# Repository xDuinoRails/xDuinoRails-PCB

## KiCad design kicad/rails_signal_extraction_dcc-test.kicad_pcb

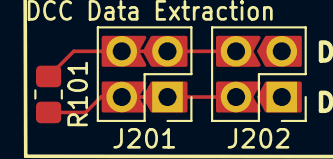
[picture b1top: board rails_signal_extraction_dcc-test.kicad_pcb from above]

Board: 2 copper layers, 3 parts (0 on the bottom side), 2 nets.

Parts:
J201, J202: Conn_02x02_Odd_Even; PinHeaderJP_2x02_P2.54mm_Vertical
R101: 22k; R_0805_2012Metric_Pad1.20x1.40mm_HandSolder

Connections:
/J_DCC1: J201.3, J201.4, J202.4, R101.1
/J_DCC_MM_SIGNAL: J201.1, J201.2, J202.2, R101.2

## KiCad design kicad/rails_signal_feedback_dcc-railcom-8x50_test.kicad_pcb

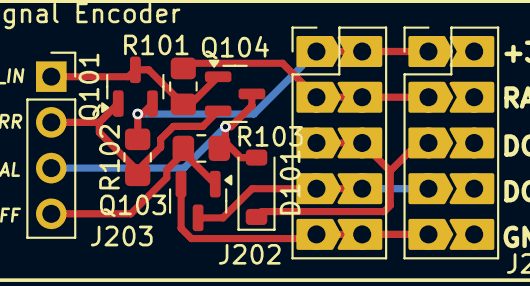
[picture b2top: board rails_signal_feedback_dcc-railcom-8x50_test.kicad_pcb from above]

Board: 2 copper layers, 10 parts (0 on the bottom side), 9 nets.

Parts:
D101: 1N5819W; D_SOD-123
J201, J202: Conn_02x05_Odd_Even; PinHeaderJP_2x05_P2.54mm_Vertical
J203: Conn_01x04; PinSocket_1x04_P2.54mm_Vertical
Q101, Q104: S8550; 8x50_SOT-23
Q103: S8050; 8x50_SOT-23
R101, R103: 10k; R_0805_2012Metric_Pad1.20x1.40mm_HandSolder
R102: 20R; R_0805_2012Metric_Pad1.20x1.40mm_HandSolder

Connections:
0: J201.9, J202.9, J202.10, Q103.1 (E)
/+J_3v3: J201.1, J202.1, J202.2, Q101.1 (E), R102.2
/J_DCC0: D101.1 (K), J201.5, J202.5, J202.6
/J_DCC1: J201.7, J202.7, J202.8, Q103.3 (C)
/J_RAILCOM_DATA: J201.3, J202.3, J202.4, R101.2
/_TST_RC_CURR: J203.2, Q101.2 (B), Q104.1 (E), R102.1
/_TST_RC_DATA_IN: J203.1, Q101.3 (C), Q104.2 (B), R101.1
/_TST_RC_ON_OFF: J203.4, Q103.2 (B), R103.2
/_TST_RC_SIGNAL: D101.2 (A), J203.3, Q104.3 (C), R103.1

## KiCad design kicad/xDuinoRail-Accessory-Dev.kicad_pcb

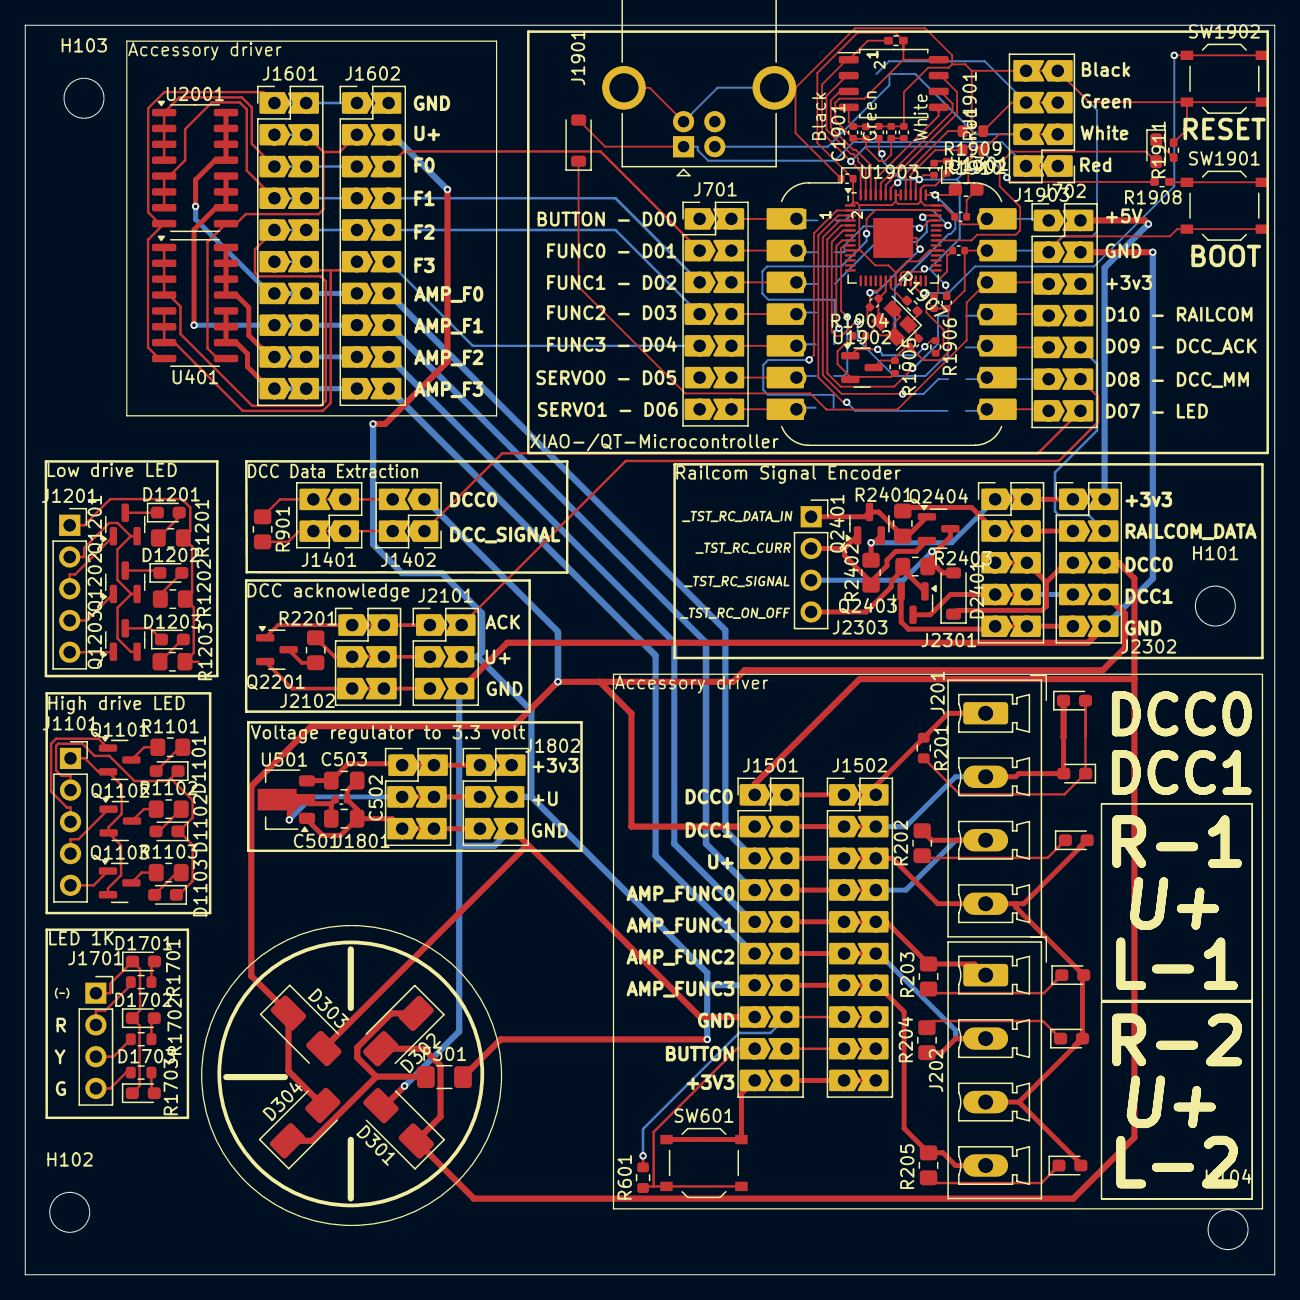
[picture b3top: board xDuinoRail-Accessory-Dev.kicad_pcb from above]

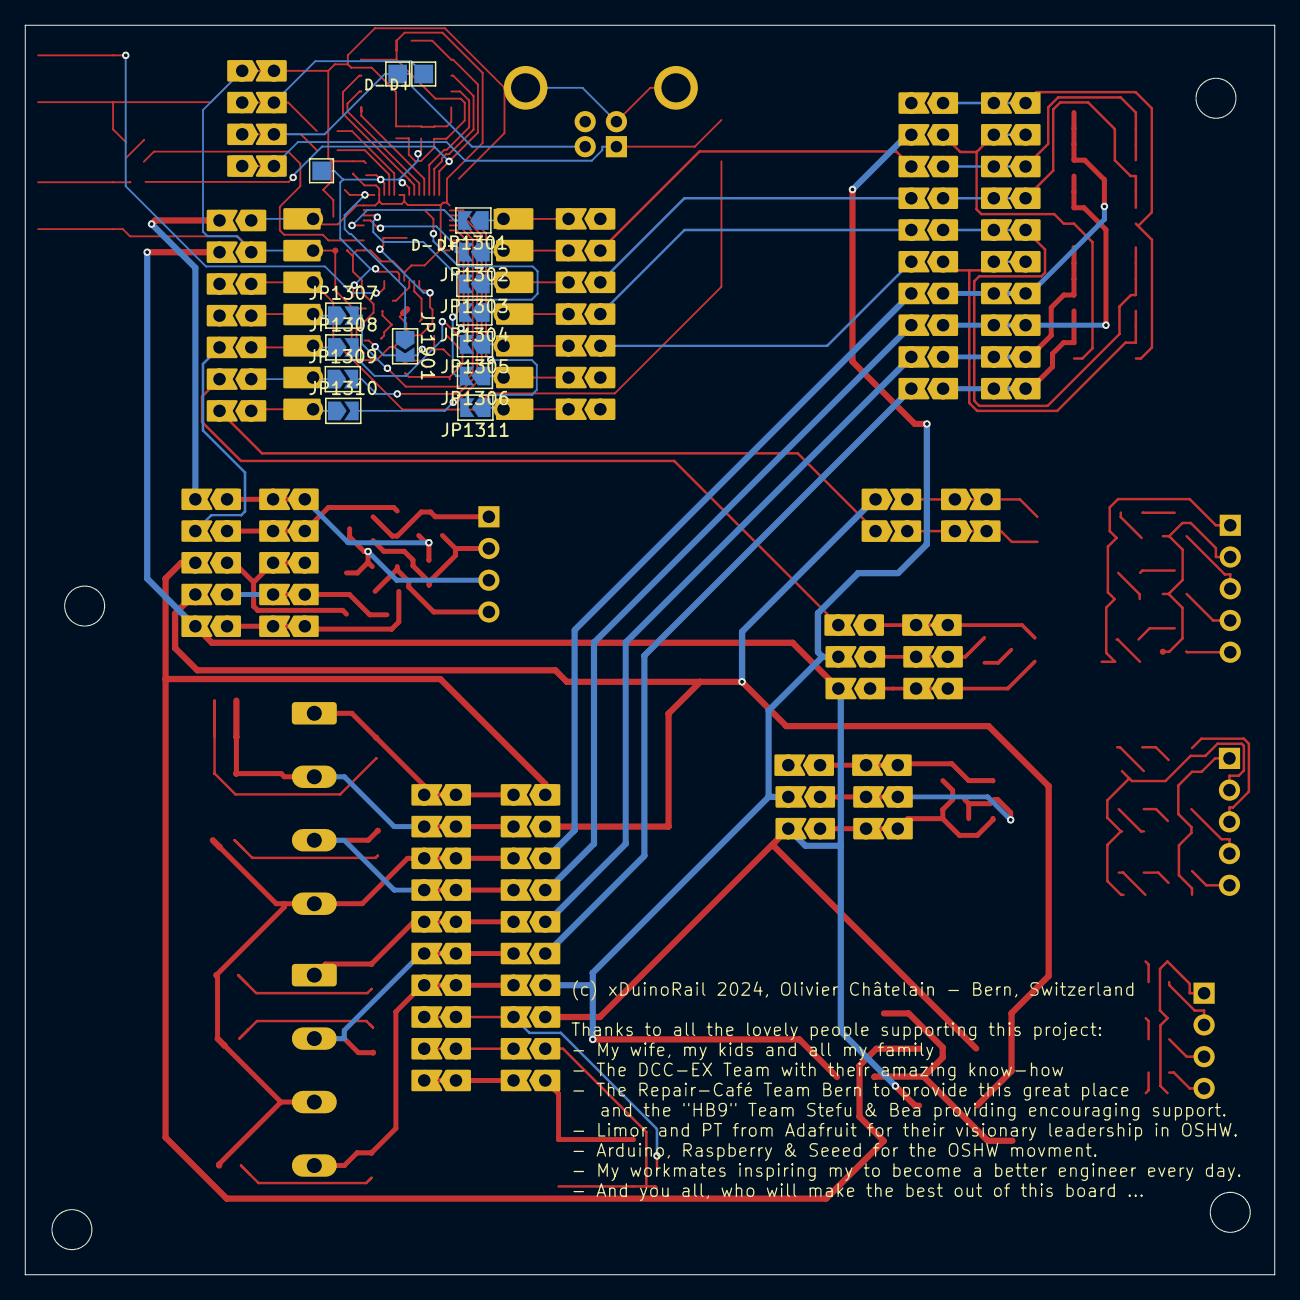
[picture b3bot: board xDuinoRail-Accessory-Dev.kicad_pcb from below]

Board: 2 copper layers, 100.0 x 100.0 mm, 132 parts (15 on the bottom side), 133 nets.

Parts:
C501, C503: 47uF; C_0805_2012Metric_Pad1.18x1.45mm_HandSolder
C502, C1907, C1909: 1u; C_0402_1005Metric
C1901, C1905, C1906, C1908, C1910, C1911, C1912, C1913, C1914, C1915: 100n; C_0402_1005Metric
C1902: 10n C0G; C_0603_1608Metric_Pad1.08x0.95mm_HandSolder
C1903, C1904: 18p; C_0402_1005Metric
D201, D1102, D1702: LED_YELLOW; LED_0603_1608Metric_Pad1.05x0.95mm_HandSolder
D202: LED_WHITE; LED_0603_1608Metric_Pad1.05x0.95mm_HandSolder
D203, D205, D1101, D1201, D1202, D1203, D1701, D1902: LED_RED; LED_0603_1608Metric_Pad1.05x0.95mm_HandSolder
D204, D206, D1103, D1703: LED_GREEN; LED_0603_1608Metric_Pad1.05x0.95mm_HandSolder
D301, D302, D303, D304: SS14; D_SMA
D1901: B5819W; D_SOD-123
D2401: 1N5819W; D_SOD-123
F301: SRF1206P150; Fuse_1206_3216Metric_Pad1.42x1.75mm_HandSolder
H101, H102, H103, H104: MountingHole; MountingHole_3.2mm_M3
J201, J202: Conn_01x04; PhoenixContact_MCV_1,5_4-G-5.08_1x04_P5.08mm_Vertical
J701, J702: Conn_02x07_Odd_Even; PinHeaderJP_2x07_P2.54mm_Vertical
J1101, J1201: Conn_01x05; PinSocket_1x05_P2.54mm_Vertical
J1401, J1402: Conn_02x02_Odd_Even; PinHeaderJP_2x02_P2.54mm_Vertical
J1501, J1502, J1601, J1602: Conn_02x10_Odd_Even; PinHeaderJP_2x10_P2.54mm_Vertical
J1701, J2303: Conn_01x04; PinSocket_1x04_P2.54mm_Vertical
J1801, J1802, J2101, J2102: Conn_02x03_Odd_Even; PinHeaderJP_2x03_P2.54mm_Vertical
J1901: USB_B; USB_B_OST_USB-B1HSxx_Horizontal
J1903: Conn_02x04_Odd_Even; PinHeaderJP_2x04_P2.54mm_Vertical
J2301, J2302: Conn_02x05_Odd_Even; PinHeaderJP_2x05_P2.54mm_Vertical
JP1301, JP1302, JP1303, JP1304, JP1305, JP1306, JP1307, JP1308, JP1309, JP1310, JP1311: SolderJumper_2_Open; SolderJumper-2_P1.3mm_Open_TrianglePad1.0x1.5mm
JP1901: VREF; SolderJumper-2_P1.3mm_Open_TrianglePad1.0x1.5mm
Q1101, Q1102, Q1103, Q2401, Q2404: S8550; 8x50_SOT-23
Q1201, Q1202, Q1203, Q2201, Q2403: S8050; 8x50_SOT-23
R201, R601: 10k; R_0603_1608Metric
R202, R203, R204, R205, R1101, R1102, R1103, R1201, R1202, R1203: 1k; R_0805_2012Metric_Pad1.20x1.40mm_HandSolder
R901: 22k; R_0805_2012Metric_Pad1.20x1.40mm_HandSolder
R1701, R1702, R1703: 1k; R_0603_1608Metric
R1901: DNP; R_0402_1005Metric_Pad0.72x0.64mm_HandSolder
R1904: 680R; R_0402_1005Metric
R1905: 3k3; R_0402_1005Metric
R1906: 150R; R_0402_1005Metric
R1907, R1908, R1911: 1k; R_0402_1005Metric_Pad0.72x0.64mm_HandSolder
R1909, R1910: 27R; R_0603_1608Metric
R2201: 150R; R_0805_2012Metric_Pad1.20x1.40mm_HandSolder
R2401, R2403: 10k; R_0805_2012Metric_Pad1.20x1.40mm_HandSolder
R2402: 20R; R_0805_2012Metric_Pad1.20x1.40mm_HandSolder
SW601: TS-1187A-B-A-B; SW_Push_1P1T_XKB_TS-1187A
SW1901: BOOTSEL; SW_Push_1P1T_XKB_TS-1187A
SW1902: RESET; SW_Push_1P1T_XKB_TS-1187A
TP1901: VREG; TestPoint_Pad_1.5x1.5mm
TP1902: D+; TestPoint_Pad_1.5x1.5mm
TP1903: D-; TestPoint_Pad_1.5x1.5mm
U401, U2001: ULN2003A; SOIC-16_3.9x9.9mm_P1.27mm
U501: HT75xx-1-SOT89; SOT-89-3
U1301: MOUDLE-SEEEDUINO-XIAO-ESP32C3; XIAO_THT_SMD
U1901: W25Q128JVSIQ; SOIC-8_5.23x5.23mm_P1.27mm
U1902: TL431DBZ; SOT-23
U1903: RP2040; QFN-56-1EP_7x7mm_P0.4mm_EP3.2x3.2mm
Y1901: ECS-120-12-36-AGN-TR3; Crystal_SMD_2520-4Pin_2.5x2.0mm

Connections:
0: J2101.5, J2102.5, J2102.6, J2301.9, J2301.10, J2302.9, Q2201.1 (E), Q2403.1 (E)
+1V1: C1905.1, C1906.1, C1907.1, TP1901.1, U1903.23 (DVDD), U1903.45 (VREG_VOUT), U1903.50 (DVDD)
+3V3: J702.2, J1101.1, J1201.1, J2302.2, Q1101.1 (E), Q1102.1 (E), Q1103.1 (E), R1201.1, R1202.1, R1203.1
+5V: D1901.1 (K), J702.5, U1301.12 (3V3)
+U: F301.2, J1501.13, J1602.4, J1802.4, J2101.4
/AMP_FUNC0: J1501.5, J1602.14
/AMP_FUNC1: J1501.7, J1602.16
/AMP_FUNC2: J1501.9, J1602.18
/AMP_FUNC3: J1501.11, J1602.20
/DCC0: D301.1 (K), D302.2 (A), J1501.1, J2302.6
/DCC1: D303.1 (K), D304.2 (A), J1402.3, J1501.3, J2302.8
/DCC_ACK: J702.12, J2101.2
/DCC_MM_SIGNAL: J702.14, J1402.1
/FUNC0: J701.3, J1602.6
/FUNC1: J701.5, J1602.8
/FUNC2: J701.7, J1602.10
/FUNC3: J701.9, J1602.12
/RAILCOM_DATA: J702.10, J2302.4
/acc-conn-screw-01x08-test/+3V3: J1501.19, SW601.1
/acc-conn-screw-01x08-test/BUTTON: J1501.17, R601.1, SW601.2
/acc-conn-screw-01x08-test/J_+3V3: J1501.20, J1502.19, J1502.20
/acc-conn-screw-01x08-test/J_AMP_FUNC0: J201.3, J1501.8, J1502.7, J1502.8, R202.1
/acc-conn-screw-01x08-test/J_AMP_FUNC1: J202.1, J1501.10, J1502.9, J1502.10, R203.1
/acc-conn-screw-01x08-test/J_AMP_FUNC2: J202.2, J1501.12, J1502.11, J1502.12, R204.1
/acc-conn-screw-01x08-test/J_AMP_FUNC3: J202.4, J1501.14, J1502.13, J1502.14, R205.1
/acc-conn-screw-01x08-test/J_BUTTON: J1501.18, J1502.17, J1502.18
/acc-conn-screw-01x08-test/J_DCC0: J201.1, J1501.2, J1502.1, J1502.2, R201.1
/acc-conn-screw-01x08-test/J_DCC1: D201.2 (A), D202.1 (K), J201.2, J1501.4, J1502.3, J1502.4
/acc-conn-screw-01x08-test/J_GND: J1501.16, J1502.15, J1502.16, R601.2
/acc-conn-screw-01x08-test/J_U+: D203.2 (A), D204.2 (A), D205.2 (A), D206.2 (A), J201.4, J202.3, J1501.6, J1502.5, J1502.6
/acc-mcu-xiao-test/J_+3v3: C1901.1, C1908.1, C1909.1, C1910.1, C1911.1, C1912.1, C1913.1, C1914.1, C1915.1, J702.1, R1901.1, R1906.2, U1301.14 (5V), U1901.8 (VCC), U1903.1 (IOVDD), U1903.10 (IOVDD), U1903.22 (IOVDD), U1903.33 (IOVDD), U1903.42 (IOVDD), U1903.44 (VREG_IN), U1903.48 (USB_VDD), U1903.49 (IOVDD)
/acc-mcu-xiao-test/J_BUTTON: J701.2, JP1301.1 (A), U1301.1 (A0)
/acc-mcu-xiao-test/J_DCC_ACK: J702.11, JP1309.1 (A), U1301.9 (A8_SCK)
/acc-mcu-xiao-test/J_DCC_MM: J702.13, JP1310.1 (A), U1301.8 (A7_RX)
/acc-mcu-xiao-test/J_FUNC0: J701.4, JP1302.1 (A), U1301.2 (A1)
/acc-mcu-xiao-test/J_FUNC1: J701.6, JP1303.1 (A), U1301.3 (A2)
/acc-mcu-xiao-test/J_FUNC2: J701.8, JP1304.1 (A), U1301.4 (A3)
/acc-mcu-xiao-test/J_FUNC3: J701.10, JP1305.1 (A), U1301.5 (A4_SDA)
/acc-mcu-xiao-test/J_GND: C1901.2, C1902.2, C1903.2, C1904.2, C1905.2, C1906.2, C1907.2, C1908.2, C1909.2, C1910.2, C1911.2, C1912.2, C1913.2, C1914.2, C1915.2, J702.3, J1901.4 (GND), J1901.5 (Shield), J1903.7, J1903.8, R1905.1, R1911.2, SW1901.2, SW1902.2, U1301.13 (GND), U1901.4 (GND), U1902.3 (A), U1903.19 (TESTEN), U1903.57 (GND), Y1901.2, Y1901.4
/acc-mcu-xiao-test/J_LED: J702.7, JP1307.1 (A), U1301.11 (A10_MOSI)
/acc-mcu-xiao-test/J_RAILCOM: J702.9, JP1308.1 (A), U1301.10 (A9_MISO)
/acc-mcu-xiao-test/J_SERVO0: J701.12, JP1306.1 (A), U1301.6 (A5_SCL)
/acc-mcu-xiao-test/J_SERVO1: J701.14, JP1311.1 (A), U1301.7 (A6_TX)
/acc-mcu-xiao-test/acc-mcu-xiao/GPIO0: JP1311.2 (B), U1903.2 (GPIO0)
/acc-mcu-xiao-test/acc-mcu-xiao/GPIO1: JP1310.2 (B), U1903.3 (GPIO1)
/acc-mcu-xiao-test/acc-mcu-xiao/GPIO2: JP1309.2 (B), U1903.4 (GPIO2)
/acc-mcu-xiao-test/acc-mcu-xiao/GPIO3: JP1307.2 (B), U1903.5 (GPIO3)
/acc-mcu-xiao-test/acc-mcu-xiao/GPIO4: JP1308.2 (B), U1903.6 (GPIO4)
/acc-mcu-xiao-test/acc-mcu-xiao/GPIO6: JP1305.2 (B), U1903.8 (GPIO6)
/acc-mcu-xiao-test/acc-mcu-xiao/GPIO7: JP1306.2 (B), U1903.9 (GPIO7)
/acc-mcu-xiao-test/acc-mcu-xiao/GPIO23: D1902.2 (A), U1903.35 (GPIO23)
/acc-mcu-xiao-test/acc-mcu-xiao/GPIO26: JP1301.2 (B), U1903.38 (GPIO26_ADC0)
/acc-mcu-xiao-test/acc-mcu-xiao/GPIO27: JP1302.2 (B), U1903.39 (GPIO27_ADC1)
/acc-mcu-xiao-test/acc-mcu-xiao/GPIO28: JP1303.2 (B), U1903.40 (GPIO28_ADC2)
/acc-mcu-xiao-test/acc-mcu-xiao/GPIO29: JP1304.2 (B), U1903.41 (GPIO29_ADC3)
/acc-mcu-xiao-test/acc-mcu-xiao/mcu_rp2040-onboard/2v5_VREF: R1904.1, R1905.2, U1902.2 (REF)
/acc-mcu-xiao-test/acc-mcu-xiao/mcu_rp2040-onboard/3V0_VREF: JP1901.2 (B), R1904.2, R1906.1, U1902.1 (K)
/acc-mcu-xiao-test/acc-mcu-xiao/mcu_rp2040-onboard/ADC_VREF: C1902.1, JP1901.1 (A), U1903.43 (ADC_AVDD)
/acc-mcu-xiao-test/acc-mcu-xiao/mcu_rp2040-onboard/D+: J1903.5, J1903.6, R1909.1, TP1902.1
/acc-mcu-xiao-test/acc-mcu-xiao/mcu_rp2040-onboard/D-: J1901.2 (D-), J1903.3, J1903.4, R1910.1, TP1903.1
/acc-mcu-xiao-test/acc-mcu-xiao/mcu_rp2040-onboard/DN: R1910.2, U1903.46 (USB_DM)
/acc-mcu-xiao-test/acc-mcu-xiao/mcu_rp2040-onboard/DP: R1909.2, U1903.47 (USB_DP)
/acc-mcu-xiao-test/acc-mcu-xiao/mcu_rp2040-onboard/QSPI_SCLK: U1901.6 (CLK), U1903.52 (QSPI_SCLK)
/acc-mcu-xiao-test/acc-mcu-xiao/mcu_rp2040-onboard/QSPI_SD0: U1901.5 (DI(IO0)), U1903.53 (QSPI_SD0)
/acc-mcu-xiao-test/acc-mcu-xiao/mcu_rp2040-onboard/QSPI_SD1: U1901.2 (DO(IO1)), U1903.55 (QSPI_SD1)
/acc-mcu-xiao-test/acc-mcu-xiao/mcu_rp2040-onboard/QSPI_SD2: U1901.3 (IO2), U1903.54 (QSPI_SD2)
/acc-mcu-xiao-test/acc-mcu-xiao/mcu_rp2040-onboard/QSPI_SD3: U1901.7 (IO3), U1903.51 (QSPI_SD3)
/acc-mcu-xiao-test/acc-mcu-xiao/mcu_rp2040-onboard/QSPI_SS: R1901.2, R1908.1, U1901.1 (~CS), U1903.56 (QSPI_SS)
/acc-mcu-xiao-test/acc-mcu-xiao/mcu_rp2040-onboard/RESET_RUN: SW1902.1, U1903.26 (RUN)
/acc-mcu-xiao-test/acc-mcu-xiao/mcu_rp2040-onboard/XIN: C1903.1, U1903.20 (XIN), Y1901.3
/acc-mcu-xiao-test/acc-mcu-xiao/mcu_rp2040-onboard/XOUT: R1907.1, U1903.21 (XOUT)
/acc-switch-driver-dual-test/J_AMP_FUNC0: J1601.13, J1601.14, J1602.13, U2001.13 (O4), U2001.14 (O3), U2001.15 (O2), U2001.16 (O1)
/acc-switch-driver-dual-test/J_AMP_FUNC1: J1601.15, J1601.16, J1602.15, U2001.10 (O7), U2001.11 (O6), U2001.12 (O5)
/acc-switch-driver-dual-test/J_AMP_FUNC2: J1601.17, J1601.18, J1602.17, U401.13 (O4), U401.14 (O3), U401.15 (O2), U401.16 (O1)
/acc-switch-driver-dual-test/J_AMP_FUNC3: J1601.19, J1601.20, J1602.19, U401.10 (O7), U401.11 (O6), U401.12 (O5)
/acc-switch-driver-dual-test/J_FUNC0: J1601.5, J1601.6, J1602.5, U2001.1 (I1), U2001.2 (I2), U2001.3 (I3), U2001.4 (I4)
/acc-switch-driver-dual-test/J_FUNC1: J1601.7, J1601.8, J1602.7, U2001.5 (I5), U2001.6 (I6), U2001.7 (I7)
/acc-switch-driver-dual-test/J_FUNC2: J1601.9, J1601.10, J1602.9, U401.1 (I1), U401.2 (I2), U401.3 (I3), U401.4 (I4)
/acc-switch-driver-dual-test/J_FUNC3: J1601.11, J1601.12, J1602.11, U401.5 (I5), U401.6 (I6), U401.7 (I7)
/acc-switch-driver-dual-test/J_GND: J1601.1, J1601.2, J1602.1, U401.8 (GND), U2001.8 (GND)
/acc-switch-driver-dual-test/J_U+: J1601.3, J1601.4, J1602.3, U401.9 (COM), U2001.9 (COM)
/led-array/LED_HIGH1: J1101.3, Q1101.2 (B)
/led-array/LED_HIGH2: J1101.4, Q1102.2 (B)
/led-array/LED_HIGH3: J1101.5, Q1103.2 (B)
/led-array/LED_LOW1: J1201.3, Q1201.2 (B)
/led-array/LED_LOW2: J1201.4, Q1202.2 (B)
/led-array/LED_LOW3: J1201.5, Q1203.2 (B)
/leds-1k-ryg/GND: D1701.1 (K), D1702.1 (K), D1703.1 (K), J1701.1
/leds-1k-ryg/LED1: J1701.2, R1701.1
/leds-1k-ryg/LED2: J1701.3, R1702.1
/leds-1k-ryg/LED3: J1701.4, R1703.1
/rails_power_ac-dc-bridge-medium-x/+U_UNFUSED: D302.1 (K), D304.1 (K), F301.1
/rails_power_dc-dc-ldo-3v3_100mA-test/J_3v3: C503.1, J1801.1, J1801.2, J1802.1, U501.3 (VOUT)
/rails_power_dc-dc-ldo-3v3_100mA-test/J_GND: C501.2, C502.2, C503.2, J1801.5, J1801.6, J1802.5, U501.1 (GND)
/rails_power_dc-dc-ldo-3v3_100mA-test/J_U+: C501.1, C502.1, J1801.3, J1801.4, J1802.3, U501.2 (VIN)
/rails_signal_combined-test/rails_signal_acknowledge_dcc-test/J_DCC_ACK: J2101.1, J2102.1, J2102.2, Q2201.2 (B)
/rails_signal_combined-test/rails_signal_acknowledge_dcc-test/J_U+: J2101.3, J2102.3, J2102.4, R2201.2
/rails_signal_combined-test/rails_signal_acknowledge_dcc-test/rails-signal-ackn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: Q2201.3 (C), R2201.1
/rails_signal_combined-test/rails_signal_extraction_dcc-test/J_DCC1: J1401.3, J1401.4, J1402.4, R901.1
/rails_signal_combined-test/rails_signal_extraction_dcc-test/J_DCC_MM_SIGNAL: J1401.1, J1401.2, J1402.2, R901.2
/rails_signal_combined-test/rails_signal_feedback_dcc-railcom-8x50_test/+J_3v3: J2301.1, J2301.2, J2302.1, Q2401.1 (E), R2402.2
/rails_signal_combined-test/rails_signal_feedback_dcc-railcom-8x50_test/J_DCC0: D2401.1 (K), J2301.5, J2301.6, J2302.5
/rails_signal_combined-test/rails_signal_feedback_dcc-railcom-8x50_test/J_DCC1: J2301.7, J2301.8, J2302.7, Q2403.3 (C)
/rails_signal_combined-test/rails_signal_feedback_dcc-railcom-8x50_test/J_RAILC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: J2301.3, J2301.4, J2302.3, R2401.2
/rails_signal_combined-test/rails_signal_feedback_dcc-railcom-8x50_test/_TST_RC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: J2303.2, Q2401.2 (B), Q2404.1 (E), R2402.1
/rails_signal_combined-test/rails_signal_feedback_dcc-railcom-8x50_test/_TST_RC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: J2303.1, Q2401.3 (C), Q2404.2 (B), R2401.1
/rails_signal_combined-test/rails_signal_feedback_dcc-railcom-8x50_test/_TST_RC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: J2303.4, Q2403.2 (B), R2403.2
/rails_signal_combined-test/rails_signal_feedback_dcc-railcom-8x50_test/_TST_RC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: D2401.2 (A), J2303.3, Q2404.3 (C), R2403.1
GND: D301.2 (A), D303.2 (A), D1101.1 (K), D1102.1 (K), D1103.1 (K), J702.4, J1101.2, J1201.2, J1501.15, J1602.2, J1802.6, J2101.6, J2302.10, Q1201.1 (E), Q1202.1 (E), Q1203.1 (E)
unnamed: C1904.1, R1907.2, Y1901.1
unnamed: D201.1 (K), D202.2 (A), R201.2
unnamed: D203.1 (K), R202.2
unnamed: D204.1 (K), R203.2
unnamed: D205.1 (K), R204.2
unnamed: D206.1 (K), R205.2
unnamed: D1101.2 (A), R1101.2
unnamed: D1102.2 (A), R1102.2
unnamed: D1103.2 (A), R1103.2
unnamed: D1201.2 (A), R1201.2
unnamed: D1201.1 (K), Q1201.3 (C)
unnamed: D1202.2 (A), R1202.2
unnamed: D1202.1 (K), Q1202.3 (C)
unnamed: D1203.2 (A), R1203.2
unnamed: D1203.1 (K), Q1203.3 (C)
unnamed: D1701.2 (A), R1701.2
unnamed: D1702.2 (A), R1702.2
unnamed: D1703.2 (A), R1703.2
unnamed: D1902.1 (K), R1911.1
unnamed: Q1101.3 (C), R1101.1
unnamed: Q1102.3 (C), R1102.1
unnamed: Q1103.3 (C), R1103.1
unnamed: R1908.2, SW1901.1
VBUS: D1901.2 (A), J1901.1 (VBUS), J1903.1, J1903.2

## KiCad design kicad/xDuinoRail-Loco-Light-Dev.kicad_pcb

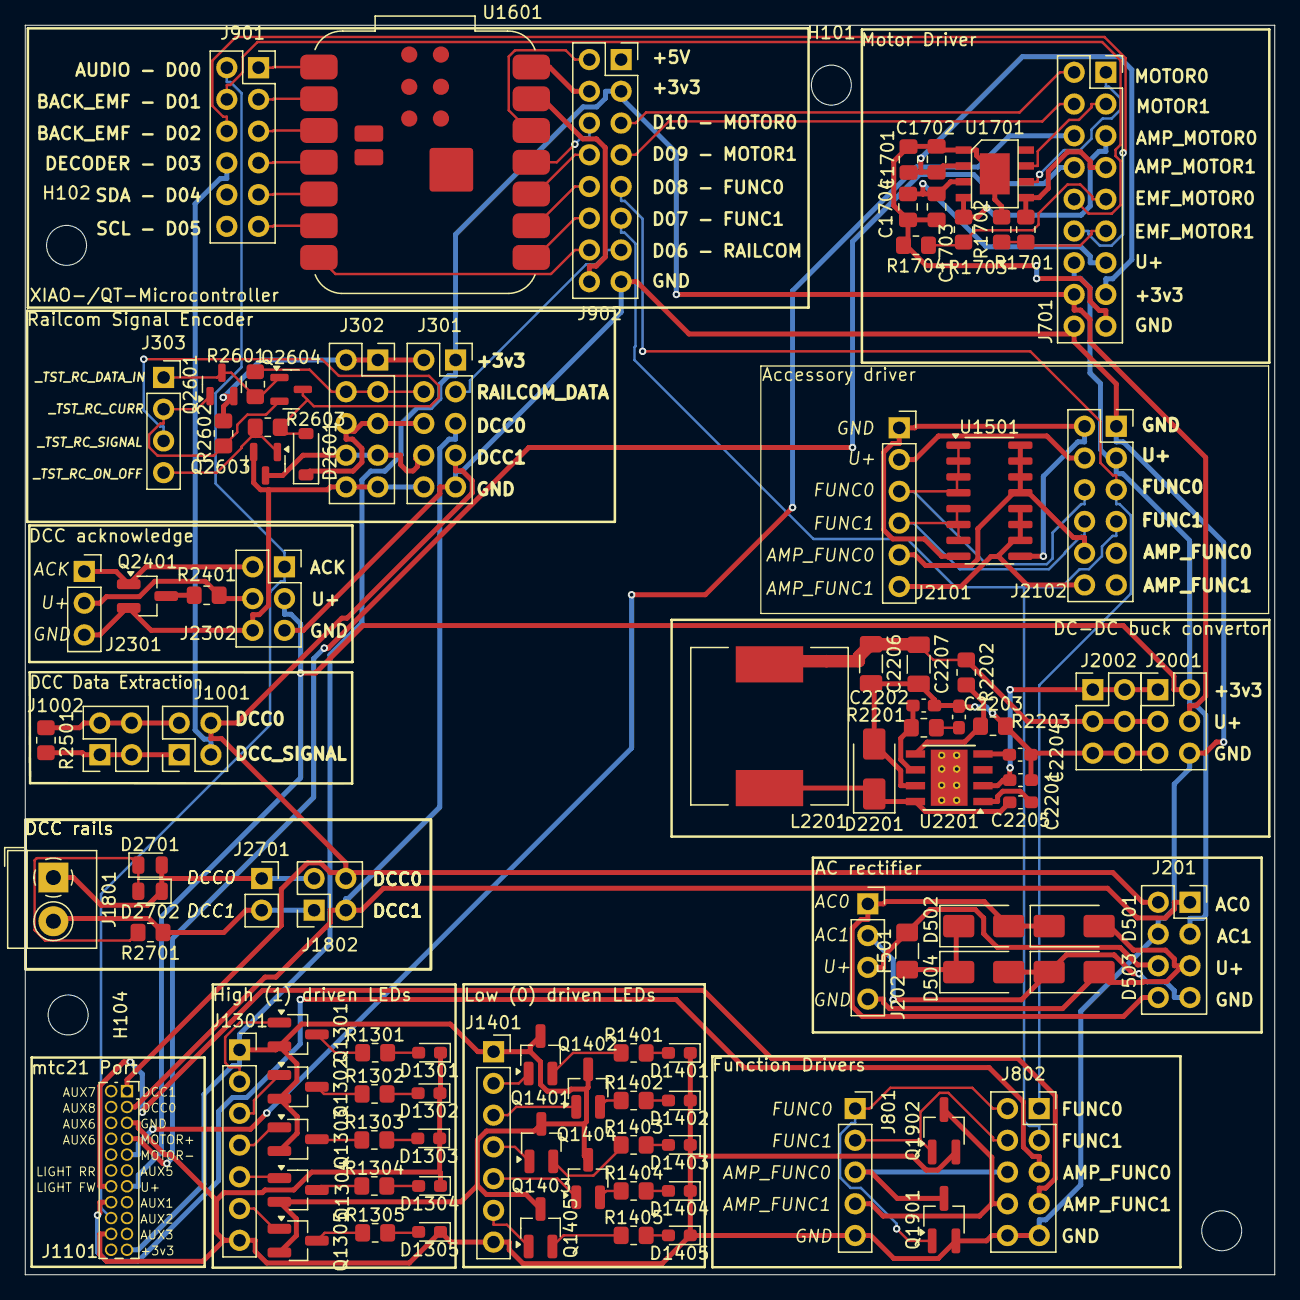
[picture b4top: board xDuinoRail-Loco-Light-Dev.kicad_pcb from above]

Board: 2 copper layers, 100.0 x 100.0 mm, 102 parts (0 on the bottom side), 112 nets.

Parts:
C1701, C1703: 10uF; C_0805_2012Metric_Pad1.18x1.45mm_HandSolder
C1702, C1704: 100nF; C_0805_2012Metric_Pad1.18x1.45mm_HandSolder
C2201: 1u; C_0603_1608Metric_Pad1.08x0.95mm_HandSolder
C2202: 10pF; C_0603_1608Metric_Pad1.08x0.95mm_HandSolder
C2203: 1nF; C_0603_1608Metric_Pad1.08x0.95mm_HandSolder
C2204, C2205: 10nF; C_0603_1608Metric_Pad1.08x0.95mm_HandSolder
C2206, C2207: 100uF; C_1206_3216Metric_Pad1.33x1.80mm_HandSolder
D501, D502, D503, D504: SS14; D_SMA
D1301, D1302, D1303, D1304, D1305, D1401, D1402, D1403, D1404, D1405: LED_RED; LED_0603_1608Metric_Pad1.05x0.95mm_HandSolder
D2201: D_Schottky; D_SMA
D2601: 1N5819W; D_SOD-123
D2701: LED_YELLOW; LED_0805_2012Metric
D2702: LED_WHITE; LED_0805_2012Metric
F501: SRF1206P150; Fuse_1206_3216Metric_Pad1.42x1.75mm_HandSolder
H101, H102, H103, H104: MountingHole; MountingHole_3.2mm_M3
J201: Conn_02x04_Odd_Even; PinSocket_2x04_P2.54mm_Vertical
J202, J303: Conn_01x04; PinSocket_1x04_P2.54mm_Vertical
J301, J302, J802: Conn_02x05_Odd_Even; PinSocket_2x05_P2.54mm_Vertical
J701: Conn_02x09_Odd_Even; PinSocket_2x09_P2.54mm_Vertical
J801: Conn_01x05; PinSocket_1x05_P2.54mm_Vertical
J901, J2102: Conn_02x06_Odd_Even; PinSocket_2x06_P2.54mm_Vertical
J902: Conn_02x08_Odd_Even; PinSocket_2x08_P2.54mm_Vertical
J1001, J1002, J1802: Conn_02x02_Odd_Even; PinSocket_2x02_P2.54mm_Vertical
J1101: 21mtc_mrkl; PinSocket_2x11_P1.27mm_Vertical
J1301, J1401: Conn_01x07; PinSocket_1x07_P2.54mm_Vertical
J1801: Conn_01x02; TerminalBlock_4Ucon_1x02_P3.50mm_Horizontal
J2001, J2002: Conn_02x03_Odd_Even; PinHeader_2x03_P2.54mm_Vertical
J2101: Conn_01x06; PinSocket_1x06_P2.54mm_Vertical
J2301: Conn_01x03; PinSocket_1x03_P2.54mm_Vertical
J2302: Conn_02x03_Odd_Even; PinSocket_2x03_P2.54mm_Vertical
J2701: Conn_01x02; PinSocket_1x02_P2.54mm_Vertical
L2201: L; L_12x12mm_H4.5mm
Q1301, Q1302, Q1303, Q1304, Q1305: S8550; 8x50_SOT-23_Handsoldering
Q1401, Q1402, Q1403, Q1404, Q1405, Q2401: S8050; 8x50_SOT-23_Handsoldering
Q1901, Q1902: AO3400A; SOT-23W_Handsoldering
Q2601, Q2604: S8550; 8x50_SOT-23
Q2603: S8050; 8x50_SOT-23
R1301, R1302, R1303, R1304, R1305, R1401, R1402, R1403, R1404, R1405, R1702, R1704: 1k; R_0805_2012Metric_Pad1.20x1.40mm_HandSolder
R1701, R1703: 6k8; R_0805_2012Metric_Pad1.20x1.40mm_HandSolder
R2201, R2202, R2203: R; R_0805_2012Metric_Pad1.20x1.40mm_HandSolder
R2401: 150R; R_0805_2012Metric_Pad1.20x1.40mm_HandSolder
R2501: 22k; R_0805_2012Metric_Pad1.20x1.40mm_HandSolder
R2601, R2603, R2701: 10k; R_0805_2012Metric_Pad1.20x1.40mm_HandSolder
R2602: 20R; R_0805_2012Metric_Pad1.20x1.40mm_HandSolder
U1501: ULN2003A; SOIC-16_3.9x9.9mm_P1.27mm
U1601: MOUDLE-SEEEDUINO-XIAO-ESP32C3; MCU_Seeed_ESP32C3
U1701: BDR6133
U2201: TPS54233; TI_SO-PowerPAD-8_ThermalVias

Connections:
0: J301.10, J302.9, J302.10, J2301.3, J2302.6, Q2401.1 (E), Q2603.1 (E)
+3V3: J301.1, J701.16, J902.3, J1101.21, J1301.1, J1401.1, J2001.4, Q1301.1 (E), Q1302.1 (E), Q1303.1 (E), Q1304.1 (E), Q1305.1 (E), Q1401.3 (C), Q1402.3 (C), Q1403.3 (C), Q1404.3 (C), Q1405.3 (C)
+U: J201.3, J701.14, J1101.13, J2001.2, J2102.3, J2302.3
/AMP_FUNC0: J802.5, J1101.16
/AMP_FUNC1: J802.7, J1101.14
/AMP_MOTOR0: J701.6, J1101.9
/AMP_MOTOR1: J701.8, J1101.7
/DCC0: J201.1, J301.5, J1101.3, J1802.2
/DCC1: J201.2, J301.7, J1001.4, J1101.1, J1802.4
/DCC_MM_SIGNAL: J901.8, J1001.2
/EMF_MOTOR0: J701.10, J901.4
/EMF_MOTOR1: J701.12, J901.6
/FUNC0: J802.1, J902.9, J2102.5
/FUNC1: J802.3, J902.11, J2102.7
/MOTOR0: J701.2, J902.5
/MOTOR1: J701.4, J902.7
/RAILCOM_DATA: J301.3, J902.13
/SPEAKER0: J901.2, J1101.18, J2302.1
/acc-switch-driver-test/J_AMP_FUNC0: J2101.5, J2102.10, U1501.13 (O4), U1501.14 (O3), U1501.15 (O2), U1501.16 (O1)
/acc-switch-driver-test/J_AMP_FUNC1: J2101.6, J2102.12, U1501.10 (O7), U1501.11 (O6), U1501.12 (O5)
/acc-switch-driver-test/J_FUNC0: J2101.3, J2102.6, U1501.1 (I1), U1501.2 (I2), U1501.3 (I3), U1501.4 (I4)
/acc-switch-driver-test/J_FUNC1: J2101.4, J2102.8, U1501.5 (I5), U1501.6 (I6), U1501.7 (I7)
/acc-switch-driver-test/J_GND: J2101.1, J2102.2, U1501.8 (GND), U1501.9 (COM)
/acc-switch-driver-test/J_U+: J2101.2, J2102.4
/led-array/LED_HIGH1: J1301.2, Q1301.2 (B)
/led-array/LED_HIGH2: J1301.3, Q1302.2 (B)
/led-array/LED_HIGH3: J1301.4, Q1303.2 (B)
/led-array/LED_HIGH4: J1301.5, Q1304.2 (B)
/led-array/LED_HIGH5: J1301.6, Q1305.2 (B)
/led-array/LED_LOW1: J1401.2, Q1401.2 (B)
/led-array/LED_LOW2: J1401.3, Q1402.2 (B)
/led-array/LED_LOW3: J1401.4, Q1403.2 (B)
/led-array/LED_LOW4: J1401.5, Q1404.2 (B)
/led-array/LED_LOW5: J1401.6, Q1405.2 (B)
/loco-driver-func-test/J_AMP_FUNC0: J801.3, J802.6, Q1901.3 (D)
/loco-driver-func-test/J_AMP_FUNC1: J801.4, J802.8, Q1902.3 (D)
/loco-driver-func-test/J_FUNC0: J801.1, J802.2, Q1901.1 (G)
/loco-driver-func-test/J_FUNC1: J801.2, J802.4, Q1902.1 (G)
/loco-driver-motor-test/J_+3v3: C1701.1, C1702.1, J701.15, U1701.2 (VCC)
/loco-driver-motor-test/J_AMP_MOTOR0: J701.5, R1703.2, U1701.4 (OUTA)
/loco-driver-motor-test/J_AMP_MOTOR1: J701.7, R1701.2, U1701.5 (OUTB)
/loco-driver-motor-test/J_EMF_MOTOR0: J701.9, R1703.1, R1704.1
/loco-driver-motor-test/J_EMF_MOTOR1: J701.11, R1701.1, R1702.1
/loco-driver-motor-test/J_MOTOR0: J701.1, U1701.6 (INA)
/loco-driver-motor-test/J_MOTOR1: J701.3, U1701.7 (INB)
/loco-driver-motor-test/J_U+: C1703.1, C1704.1, J701.13, U1701.3 (VM)
/loco-mcu-xiao-test/J_+3v3: J902.4, U1601.14 (5V)
/loco-mcu-xiao-test/J_+5V: J902.2, U1601.12 (3V3)
/loco-mcu-xiao-test/J_AUDIO: J901.1, U1601.1 (A0)
/loco-mcu-xiao-test/J_BACK_EMF0: J901.3, U1601.2 (A1)
/loco-mcu-xiao-test/J_BACK_EMF1: J901.5, U1601.3 (A2)
/loco-mcu-xiao-test/J_DECODER: J901.7, U1601.4 (A3)
/loco-mcu-xiao-test/J_FUNC0: J902.10, U1601.9 (A8_SCK)
/loco-mcu-xiao-test/J_FUNC1: J902.12, U1601.8 (A7_RX)
/loco-mcu-xiao-test/J_GND: J902.16, U1601.13 (GND)
/loco-mcu-xiao-test/J_I2C.SCL: J901.11, U1601.6 (A5_SCL)
/loco-mcu-xiao-test/J_I2C.SDA: J901.9, U1601.5 (A4_SDA)
/loco-mcu-xiao-test/J_MOTOR0: J902.6, U1601.11 (A10_MOSI)
/loco-mcu-xiao-test/J_MOTOR1: J902.8, U1601.10 (A9_MISO)
/loco-mcu-xiao-test/J_RAILCOM: J902.14, U1601.7 (A6_TX)
/rails-connector-3_5mm-test/J_DCC0: J1801.2, J1802.1, J2701.2, R2701.1
/rails-connector-3_5mm-test/J_DCC1: D2701.2 (A), D2702.1 (K), J1801.1, J1802.3, J2701.1
/rails_power_ac-dc-medium-3v3_100mA/rails_power_ac-dc-bridge-medium-test/J_AC0: D501.1 (K), D502.2 (A), J201.8, J202.1
/rails_power_ac-dc-medium-3v3_100mA/rails_power_ac-dc-bridge-medium-test/J_AC1: D503.1 (K), D504.2 (A), J201.7, J202.2
/rails_power_ac-dc-medium-3v3_100mA/rails_power_ac-dc-bridge-medium-test/J_GND: D501.2 (A), D503.2 (A), J201.5, J202.4
/rails_power_ac-dc-medium-3v3_100mA/rails_power_ac-dc-bridge-medium-test/J_U+: F501.2, J201.6, J202.3
/rails_power_ac-dc-medium-3v3_100mA/rails_power_ac-dc-bridge-medium-test/rails_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: D502.1 (K), D504.1 (K), F501.1
/rails_power_ac-dc-medium-3v3_100mA/rails_power_dc-dc-ldo-3v3_3A-test/J_+3V3: C2206.1, C2207.1, J2001.3, J2002.3, J2002.4, L2201.2, R2202.1
/rails_power_ac-dc-medium-3v3_100mA/rails_power_dc-dc-ldo-3v3_3A-test/J_GND: C2201.2, C2202.2, C2203.2, C2204.2, C2206.2, C2207.2, D2201.2 (A), J2001.5, J2002.5, J2002.6, R2203.2, U2201.7 (GND)
/rails_power_ac-dc-medium-3v3_100mA/rails_power_dc-dc-ldo-3v3_3A-test/J_U+: C2201.1, J2001.1, J2002.1, J2002.2, U2201.2 (VIN)
/rails_power_ac-dc-medium-3v3_100mA/rails_power_dc-dc-ldo-3v3_3A-test/rails_pow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: C2205.1, U2201.1 (BOOT)
/rails_power_ac-dc-medium-3v3_100mA/rails_power_dc-dc-ldo-3v3_3A-test/rails_pow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: C2202.1, R2201.2, U2201.6 (COMP)
/rails_power_ac-dc-medium-3v3_100mA/rails_power_dc-dc-ldo-3v3_3A-test/rails_pow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: R2202.2, R2203.1, U2201.5 (FB)
/rails_power_ac-dc-medium-3v3_100mA/rails_power_dc-dc-ldo-3v3_3A-test/rails_pow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: C2205.2, D2201.1 (K), L2201.1, U2201.8 (PH)
/rails_power_ac-dc-medium-3v3_100mA/rails_power_dc-dc-ldo-3v3_3A-test/rails_pow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: C2204.1, U2201.4 (SS)
/rails_signal_acknowledge_dcc-test/J_DCC_ACK: J2301.1, J2302.2, Q2401.2 (B)
/rails_signal_acknowledge_dcc-test/J_U+: J2301.2, J2302.4, R2401.2
/rails_signal_acknowledge_dcc-test/rails-signal-acknowledge_dcc/U+_DROP: Q2401.3 (C), R2401.1
/rails_signal_extraction_dcc-test/J_DCC1: J1001.3, J1002.3, J1002.4, R2501.1
/rails_signal_extraction_dcc-test/J_DCC_MM_SIGNAL: J1001.1, J1002.1, J1002.2, R2501.2
/rails_signal_feedback_dcc-railcom-8x50_test/+J_3v3: J301.2, J302.1, J302.2, Q2601.1 (E), R2602.2
/rails_signal_feedback_dcc-railcom-8x50_test/J_DCC0: D2601.1 (K), J301.6, J302.5, J302.6
/rails_signal_feedback_dcc-railcom-8x50_test/J_DCC1: J301.8, J302.7, J302.8, Q2603.3 (C)
/rails_signal_feedback_dcc-railcom-8x50_test/J_RAILCOM_DATA: J301.4, J302.3, J302.4, R2601.2
/rails_signal_feedback_dcc-railcom-8x50_test/_TST_RC_CURR: J303.2, Q2601.2 (B), Q2604.1 (E), R2602.1
/rails_signal_feedback_dcc-railcom-8x50_test/_TST_RC_DATA_IN: J303.1, Q2601.3 (C), Q2604.2 (B), R2601.1
/rails_signal_feedback_dcc-railcom-8x50_test/_TST_RC_ON_OFF: J303.4, Q2603.2 (B), R2603.2
/rails_signal_feedback_dcc-railcom-8x50_test/_TST_RC_SIGNAL: D2601.2 (A), J303.3, Q2604.3 (C), R2603.1
GND: D1301.1 (K), D1302.1 (K), D1303.1 (K), D1304.1 (K), D1305.1 (K), D1401.1 (K), D1402.1 (K), D1403.1 (K), D1404.1 (K), D1405.1 (K), J201.4, J301.9, J701.18, J801.5, J802.9, J802.10, J902.15, J1101.5, J1101.20, J1301.7, J1401.7, J2001.6, J2102.1, J2302.5, Q1901.2 (S), Q1902.2 (S)
unnamed: C2203.1, R2201.1
unnamed: D1301.2 (A), R1301.2
unnamed: D1302.2 (A), R1302.2
unnamed: D1303.2 (A), R1303.2
unnamed: D1304.2 (A), R1304.2
unnamed: D1305.2 (A), R1305.2
unnamed: D1401.2 (A), R1401.2
unnamed: D1402.2 (A), R1402.2
unnamed: D1403.2 (A), R1403.2
unnamed: D1404.2 (A), R1404.2
unnamed: D1405.2 (A), R1405.2
unnamed: D2701.1 (K), D2702.2 (A), R2701.2
unnamed: Q1301.3 (C), R1301.1
unnamed: Q1302.3 (C), R1302.1
unnamed: Q1303.3 (C), R1303.1
unnamed: Q1304.3 (C), R1304.1
unnamed: Q1305.3 (C), R1305.1
unnamed: Q1401.1 (E), R1401.1
unnamed: Q1402.1 (E), R1402.1
unnamed: Q1403.1 (E), R1403.1
unnamed: Q1404.1 (E), R1404.1
unnamed: Q1405.1 (E), R1405.1
PGND: C1701.2, C1702.2, C1703.2, C1704.2, J701.17, R1702.2, R1704.2, U1701.1 (GND), U1701.9 (PGND)

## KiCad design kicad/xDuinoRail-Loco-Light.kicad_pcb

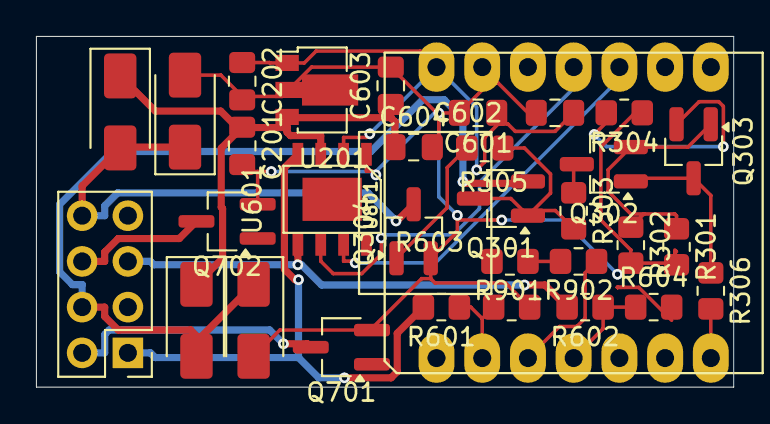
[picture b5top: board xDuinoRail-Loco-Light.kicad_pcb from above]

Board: 2 copper layers, 38.7 x 19.5 mm, 32 parts (0 on the bottom side), 23 nets.

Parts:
C201: 1uF; C_0805_2012Metric_Pad1.18x1.45mm_HandSolder
C202: 47uF; C_0805_2012Metric_Pad1.18x1.45mm_HandSolder
C601, C603: 10uF; C_0805_2012Metric_Pad1.18x1.45mm_HandSolder
C602, C604: 100nF; C_0805_2012Metric_Pad1.18x1.45mm_HandSolder
D401, D402, D403, D404: SS14; D_SMA
J501: Conn_02x04_Counter_Clockwise; PinHeader_2x04_P2.54mm_Vertical
Q301, Q304: S8050; 8x50_SOT-23_Handsoldering
Q302, Q303: S8550; 8x50_SOT-23_Handsoldering
Q701, Q702: AO3400A; SOT-23W_Handsoldering
R301, R302, R304: 10R; R_0805_2012Metric_Pad1.20x1.40mm_HandSolder
R303: 0R; R_0805_2012Metric_Pad1.20x1.40mm_HandSolder
R305, R306, R901, R902: 10k; R_0805_2012Metric_Pad1.20x1.40mm_HandSolder
R601, R602: 6k8; R_0805_2012Metric_Pad1.20x1.40mm_HandSolder
R603, R604: 1k; R_0805_2012Metric_Pad1.20x1.40mm_HandSolder
U201: HT7533-1; SOT-89-3
U601: BDR6133
U801: MOUDLE-SEEEDUINO-XIAO-ESP32C3; MOUDLE14P-SMD-2.54-21X17.8MM

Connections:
+3V3: C202.1, C601.1, C602.1, U201.1 (OUT), U601.2 (VCC), U801.14 (5V)
+U: C201.1, C603.1, C604.1, D402.1 (K), D404.1 (K), U201.3 (IN), U601.3 (VM)
/loco-adapter-nem652-8-pin/AMP_FUNC0: J501.2, Q701.3 (D)
/loco-adapter-nem652-8-pin/AMP_FUNC1: J501.6, Q702.3 (D)
/loco-adapter-nem652-8-pin/AMP_MOTOR0: J501.1, R601.2, U601.4 (OUTA)
/loco-adapter-nem652-8-pin/AMP_MOTOR1: J501.5, R602.2, U601.5 (OUTB)
/loco-driver-motor/EMF_MOTOR0: R601.1, R603.1, U801.2 (A1)
/loco-driver-motor/EMF_MOTOR1: R602.1, R604.1, U801.4 (A3)
/loco-driver-motor/MOTOR0: U601.6 (INA), U801.11 (A10_MOSI)
/loco-driver-motor/MOTOR1: U601.7 (INB), U801.10 (A9_MISO)
/loco-mcu-xiao/DECODER: R902.2, U801.3 (A2)
/loco-mcu-xiao/RAILCOM: R306.2, U801.7 (A6_TX)
/rails_signal_feedback_dcc-railcom-8x50/15R: R301.2, R302.2, R304.1
/rails_signal_feedback_dcc-railcom-8x50/+3V3: Q303.1 (E), R304.2
/rails_signal_feedback_dcc-railcom-8x50/DCC0: D401.1 (K), D402.2 (A), J501.8, Q304.3 (C)
/rails_signal_feedback_dcc-railcom-8x50/DCC1: D403.1 (K), D404.2 (A), J501.4, Q301.1 (E)
/rails_signal_feedback_dcc-railcom-8x50/RC_CURR: Q302.1 (E), Q303.2 (B), R301.1, R302.1
/rails_signal_feedback_dcc-railcom-8x50/RC_DATA_IN: Q302.2 (B), Q303.3 (C), R306.1
/rails_signal_feedback_dcc-railcom-8x50/RC_J_SIGNAL: Q301.2 (B), Q301.3 (C), R303.2, R305.1
/rails_signal_feedback_dcc-railcom-8x50/RC_ON_OFF: Q304.2 (B), R305.2
/rails_signal_feedback_dcc-railcom-8x50/RC_SIGNAL: Q302.3 (C), R303.1
GND: C201.2, C202.2, C601.2, C602.2, C603.2, C604.2, D401.2 (A), D403.2 (A), Q304.1 (E), Q701.2 (S), Q702.2 (S), R603.2, R604.2, U201.2 (GND), U601.1 (GND), U801.13 (GND)
unnamed: R901.2, R902.1
